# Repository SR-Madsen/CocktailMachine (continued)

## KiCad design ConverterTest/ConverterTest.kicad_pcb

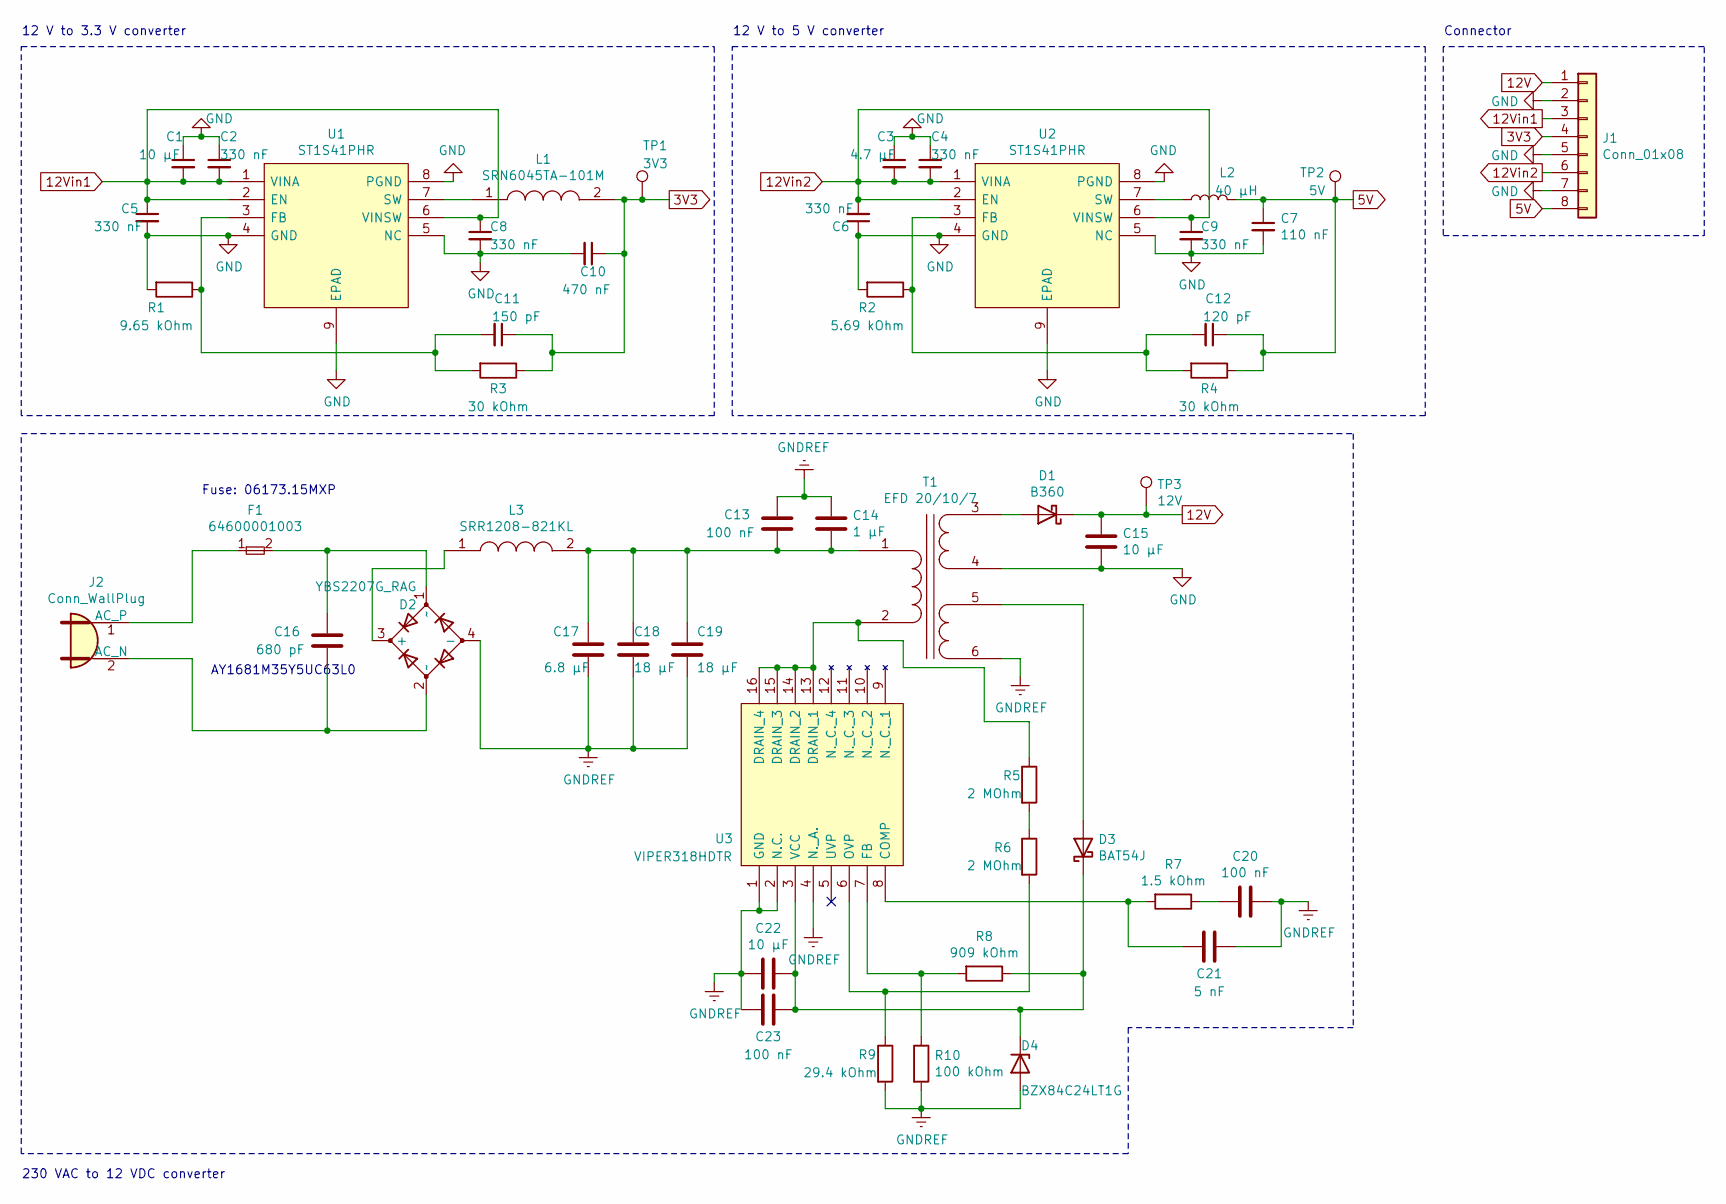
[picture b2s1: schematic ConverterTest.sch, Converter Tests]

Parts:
C1, C15, C22: 10 µF; C_1206_3216Metric
C2, C4, C5, C6, C8, C9: 330 nF; C_0603_1608Metric
C3: 4.7 µF; C_0805_2012Metric
C7: 110 nF; C_0603_1608Metric
C10: 470 nF; C_0603_1608Metric
C11: 150 pF; C_0603_1608Metric
C12: 120 pF; C_0603_1608Metric
C13: 100 nF; C_1210_3225Metric
C14: 1 µF; C_Rect_L24.0mm_W10.1mm_P22.50mm_MKT
C16: 680 pF; C_Disc_D8.0mm_W5.0mm_P10.00mm
C17: 6.8 µF; CP_Radial_D10.0mm_P5.00mm
C18, C19: 18 µF; CP_Radial_D12.5mm_P5.00mm
C20, C23: 100 nF; C_0603_1608Metric
C21: 5 nF; C_0603_1608Metric
D1: B360; D_SMC
D2: YBS2207G_RAG; Mouser Part Number 821-YBS2207GRAG
D3: BAT54J; D_SOD-323F
D4: BZX84C24LT1G; D_SOT-23_ANK
F1: 64600001003; Mouser Part Number 576-64600001003
J1: Conn_01x08; PinHeader_1x08_P2.54mm_Vertical
J2: Conn_WallPlug; PinHeader_1x02_P2.54mm_Vertical
L1: SRN6045TA-101M; Mouser Part Number 652-SRN6045TA-101M
L2: 40 µH; L_Bourns-SRN4018
L3: SRR1208-821KL; Mouser Part Number 652-SRR1208-821KL
R1: 9.65 kOhm; R_0603_1608Metric
R2: 5.69 kOhm; R_0603_1608Metric
R3, R4: 30 kOhm; R_0603_1608Metric
R5, R6: 2 MOhm; R_1206_3216Metric
R7: 1.5 kOhm; R_0603_1608Metric
R8: 909 kOhm; R_0603_1608Metric
R9: 29.4 kOhm; R_0603_1608Metric
R10: 100 kOhm; R_0603_1608Metric
T1: EFD 20/10/7; EFD_20_10_7
TP1: 3V3; TestPoint_Pad_D2.0mm
TP2: 5V; TestPoint_Pad_D2.0mm
TP3: 12V; TestPoint_Pad_D2.0mm
U1, U2: ST1S41PHR; Manufacturer_Part_Number ST1S41PHR
U3: VIPER318HDTR; Manufacturer_Part_Number VIPER318HDTR

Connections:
3V3: C10.1, C11.1, J1.4, L1.2, R3.1, TP1.1
5V: C7.1, C12.1, J1.8, L2.2, R4.1, TP2.1
12V: C15.1, D1.1 (K), J1.1, TP3.1
12Vin1: C1.2, C2.2, C5.1, C8.1, J1.3, U1.1 (VINA), U1.2 (EN), U1.6 (VINSW)
12Vin2: C3.2, C4.2, C6.2, C9.1, J1.6, U2.1 (VINA), U2.2 (EN), U2.6 (VINSW)
GND: C1.1, C2.1, C3.1, C4.1, C5.2, C6.1, C7.2, C8.2, C9.2, C10.2, C15.2, J1.2, J1.5, J1.7, R1.2, R2.2, T1.4 (SB), U1.4 (GND), U1.5 (NC), U1.8 (PGND), U1.9 (EPAD), U2.4 (GND), U2.5 (NC), U2.8 (PGND), U2.9 (EPAD)
GNDREF: C13.1, C14.1, C17.2, C18.2, C19.2, C20.1, C21.1, C22.2, C23.2, D2.4 (-), D4.2 (A), R9.2, R10.2, T1.6 (SD), U3.1 (GND), U3.2 (N.C.), U3.4 (N._A.)
unnamed: C11.2, R1.1, R3.2, U1.3 (FB)
unnamed: C12.2, R2.1, R4.2, U2.3 (FB)
unnamed: C13.2, C14.2, C17.1, C18.1, C19.1, L3.2, T1.1 (AA)
unnamed: C16.1, D2.1 (~~), F1.2
unnamed: C16.2, D2.2 (~~), J2.2 (AC_N)
unnamed: C20.2, R7.1
unnamed: C21.2, R7.2, U3.8 (COMP)
unnamed: C22.1, C23.1, D3.1 (K), D4.1 (K), R8.1, U3.3 (VCC)
unnamed: D1.2 (A), T1.3 (SA)
unnamed: D2.3 (+), L3.1
unnamed: D3.2 (A), T1.5 (SC)
unnamed: F1.1, J2.1 (AC_P)
unnamed: L1.1, U1.7 (SW)
unnamed: L2.1, U2.7 (SW)
unnamed: R5.1, T1.2 (AB), U3.13 (DRAIN_1), U3.14 (DRAIN_2), U3.15 (DRAIN_3), U3.16 (DRAIN_4)
unnamed: R5.2, R6.1
unnamed: R6.2, R9.1, U3.6 (OVP)
unnamed: R8.2, R10.1, U3.7 (FB)

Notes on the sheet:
12 V to 3.3 V converter
12 V to 5 V converter
Fuse: 06173.15MXP
AY1681M35Y5UC63L0
230 VAC to 12 VDC converter
Connector

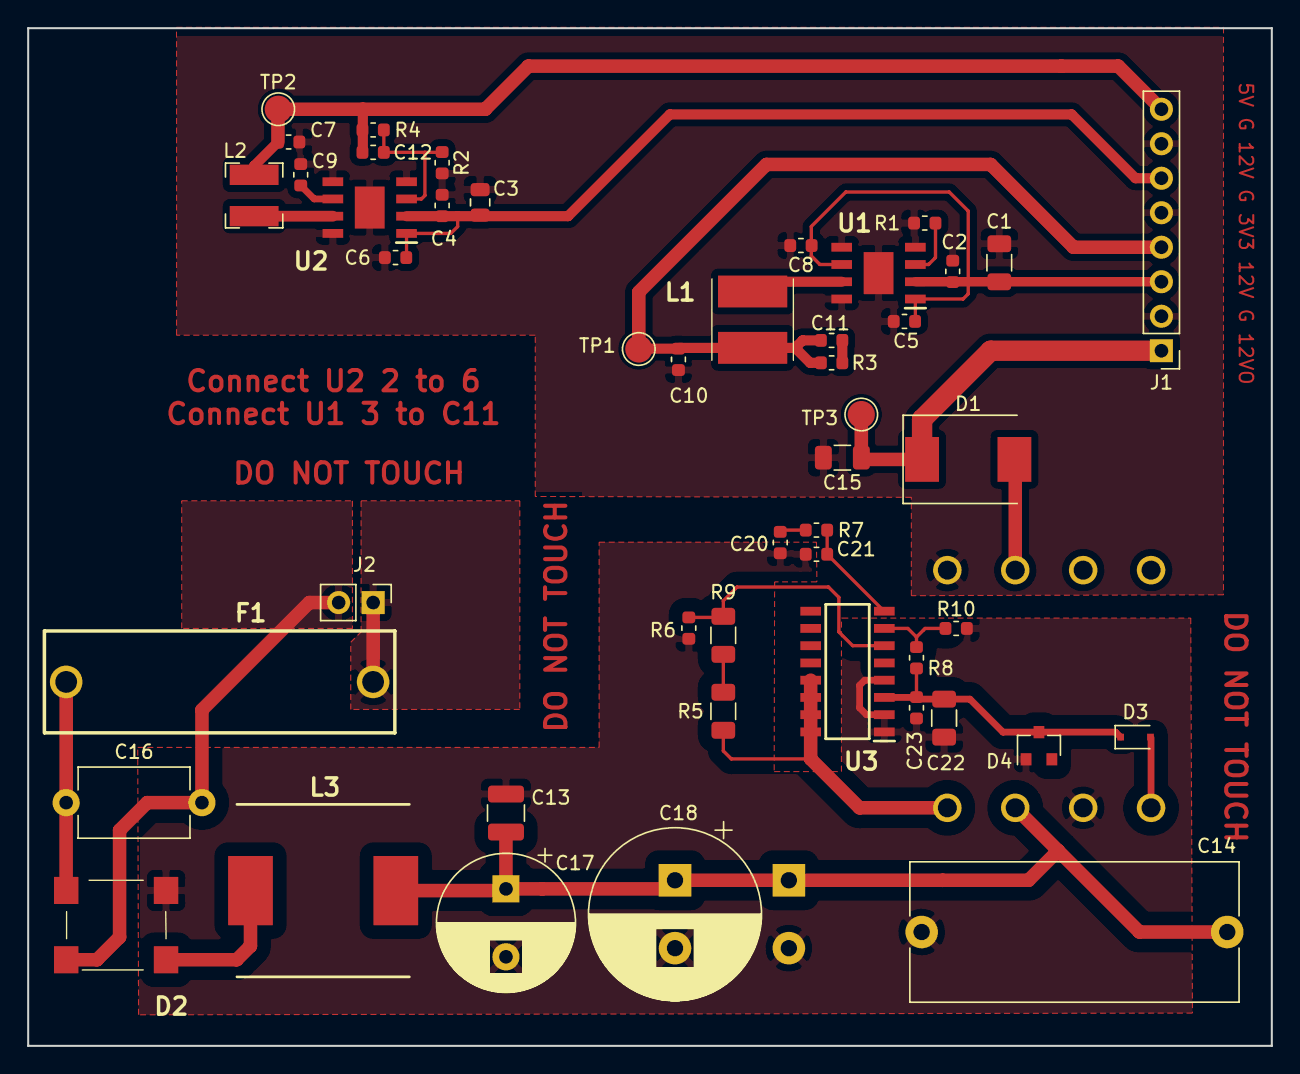
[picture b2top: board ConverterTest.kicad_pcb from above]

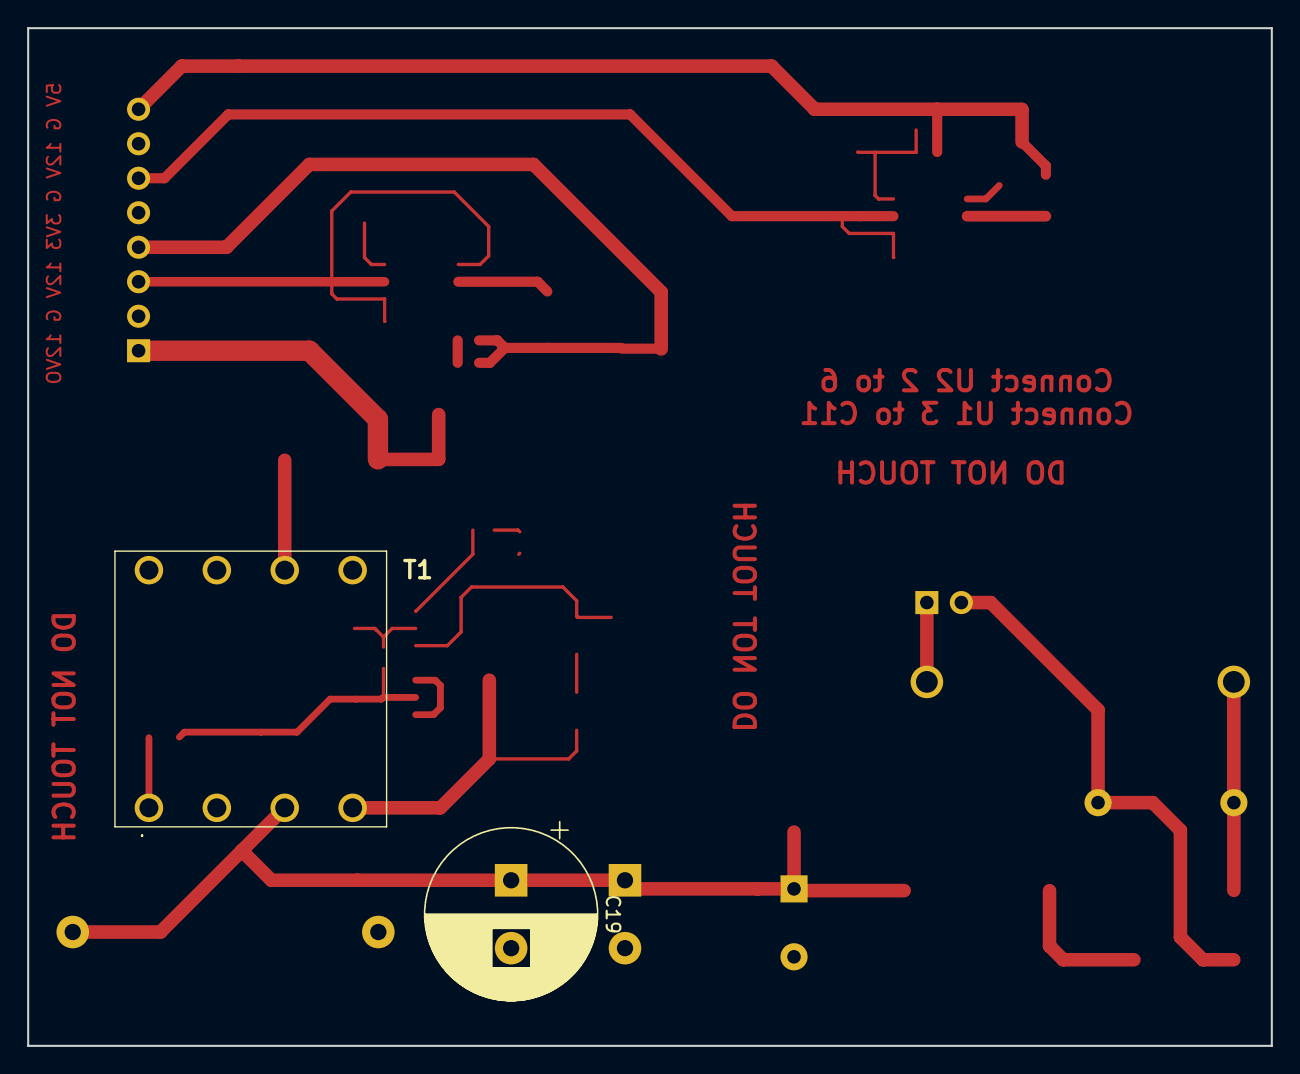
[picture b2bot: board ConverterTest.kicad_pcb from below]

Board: 2 copper layers, 91.6 x 74.9 mm, 50 parts (2 on the bottom side), 25 nets.

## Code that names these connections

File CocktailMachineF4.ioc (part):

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PB13.GPIOParameters=GPIO_PuPd,GPIO_Label
PB10.Mode=Single Bank 1
PG4.Signal=FMC_A14_BA0
PG8.Signal=FMC_SDCLK
PC12.Signal=UART5_TX
PB14.GPIO_Label=LCD_BL_CTRL
PG0.Signal=FMC_A10
PA6.GPIO_Label=LED_YELLOW
PB13.Signal=GPIO_Input
PE6.GPIO_Label=PUMP4_ON
RCC.SYSCLKSource=RCC_SYSCLKSOURCE_PLLCLK
PF7.Signal=QUADSPI_BK1_IO2
PB6.Signal=I2C1_SCL
PB12.PinState=GPIO_PIN_SET
PH1/OSC_OUT.Signal=RCC_OSC_OUT
PB6.Mode=I2C
PC3.Signal=FMC_SDCKE0
PD0.Signal=FMC_D2_DA2
PD8.Signal=FMC_D13_DA13
PE5.Signal=GPIO_Output
PE1.Signal=FMC_NBL1
PB3.Mode=JTAG_5_pins
PB12.GPIO_Label=DSI_RESET
PE9.Signal=FMC_D6_DA6
PA5.GPIO_PuPd=GPIO_PULLDOWN
PE4.GPIO_Label=PUMP2_ON
PF8.Mode=Single Bank 1
PF3.Signal=FMC_A3
PE10.Signal=FMC_D7_DA7
PC8.GPIOParameters=GPIO_Speed,GPIO_Label
Mcu.Package=LQFP176
PA5.GPIOParameters=GPIO_PuPd,GPIO_Label
PC8.GPIO_Speed=GPIO_SPEED_FREQ_LOW
PB14.GPIOParameters=GPIO_Label
PF14.Signal=FMC_A8
PF10.Mode=Single Bank 1
PE6.GPIO_PuPd=GPIO_PULLDOWN
PD15.Signal=FMC_D1_DA1
PA6.GPIOParameters=GPIO_Label
PG5.Signal=FMC_A15_BA1
PC2.Signal=FMC_SDNE0
PD1.Signal=FMC_D3_DA3
PC0.Signal=FMC_SDNWE
PD10.Signal=FMC_D15_DA15
PB11.Mode=DSIHost_Adapted_TE
PB10.Signal=QUADSPI_BK1_NCS
PB14.Signal=GPIO_Input
PA5.Signal=GPIO_Output
PC12.Mode=Asynchronous
PB13.GPIO_PuPd=GPIO_NOPULL
PE14.Signal=FMC_D11_DA11
PE15.Signal=FMC_D12_DA12
PE8.Signal=FMC_D5_DA5
PF13.Signal=FMC_A7
PA13.Mode=JTAG_5_pins
PE4.GPIO_PuPd=GPIO_PULLDOWN
PA5.GPIO_Label=LED_RED
PE5.GPIO_Label=PUMP3_ON
PF6.Mode=Single Bank 1
PF9.Signal=QUADSPI_BK1_IO1
PE3.Signal=GPIO_Output
PF4.Signal=FMC_A4
PD2.Signal=UART5_RX
PB12.GPIO_PuPd=GPIO_PULLUP
PA7.GPIOParameters=GPIO_Label
PB12.GPIOParameters=GPIO_Speed,PinState,GPIO_PuPd,GPIO_Label
PC3.Mode=SdramChipSelect1_1
Mcu.UserName=STM32F469IITx
PB13.GPIO_Label=LCD_INT
PB11.Signal=DSIHOST_TE
PG15.Signal=FMC_SDNCAS
PE5.GPIOParameters=GPIO_PuPd,GPIO_Label
PE4.GPIOParameters=GPIO_PuPd,GPIO_Label
PE5.GPIO_PuPd=GPIO_PULLDOWN
PH0/OSC_IN.Mode=HSE-External-Oscillator
PF12.Signal=FMC_A6
RCC.HSE_VALUE=10000000
PA15.Mode=JTAG_5_pins
PF9.Mode=Single Bank 1
PB4.Mode=JTAG_5_pins
PE13.Signal=FMC_D10_DA10
PA14.Mode=JTAG_5_pins
PF11.Signal=FMC_SDNRAS
PE3.GPIOParameters=GPIO_Label
PB7.Signal=I2C1_SDA
PE4.Signal=GPIO_Output
PH1/OSC_OUT.Mode=HSE-External-Oscillator
PE6.GPIOParameters=GPIO_PuPd,GPIO_Label
PA6.Signal=GPIO_Output
PA15.Signal=SYS_JTDI
PF8.Signal=QUADSPI_BK1_IO0
PF5.Signal=FMC_A5
PF0.Signal=FMC_A0
PE7.Signal=FMC_D4_DA4
PB4.Signal=SYS_JTRST
PA3.Signal=ADCx_IN3
PG1.Signal=FMC_A11
PC8.Signal=GPIO_Output
PC2.Mode=SdramChipSelect1_1
PD9.Signal=FMC_D14_DA14
PC8.GPIO_Label=BT_RESET
PA13.Signal=SYS_JTMS-SWDIO
PF7.Mode=Single Bank 1
PF6.Signal=QUADSPI_BK1_IO3
PF2.Signal=FMC_A2
PE11.Signal=FMC_D8_DA8
PB12.GPIO_Speed=GPIO_SPEED_FREQ_VERY_HIGH
PD2.Mode=Asynchronous
board=custom
PH0/OSC_IN.Signal=RCC_OSC_IN
PF10.Signal=QUADSPI_CLK
PF15.Signal=FMC_A9
PF1.Signal=FMC_A1
PE6.Signal=GPIO_Output
Mcu.Name=STM32F469IITx
PE0.Signal=FMC_NBL0
PE12.Signal=FMC_D9_DA9
PD14.Signal=FMC_D0_DA0
PB3.Signal=SYS_JTDO-SWO
RCC.SYSCLKFreq_VALUE=180000000
PA7.GPIO_Label=LED_GREEN
PB7.Mode=I2C
PA14.Signal=SYS_JTCK-SWCLK
PE3.GPIO_Label=PUMP1_ON
PB12.Signal=GPIO_Output
PA7.Signal=GPIO_Output

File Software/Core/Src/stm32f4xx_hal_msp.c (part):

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
    __HAL_RCC_GPIOA_CLK_ENABLE();
    /**ADC1 GPIO Configuration
    PA3     ------> ADC1_IN3
    */
    GPIO_InitStruct.Pin = GPIO_PIN_3;
    GPIO_InitStruct.Mode = GPIO_MODE_ANALOG;
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    __HAL_RCC_ADC1_CLK_DISABLE();

    /**ADC1 GPIO Configuration
    PA3     ------> ADC1_IN3
    */
    HAL_GPIO_DeInit(GPIOA, GPIO_PIN_3);

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
    __HAL_RCC_GPIOB_CLK_ENABLE();
    /**DSIHOST GPIO Configuration
    PB11     ------> DSIHOST_TE
    */
    GPIO_InitStruct.Pin = GPIO_PIN_11;
    GPIO_InitStruct.Mode = GPIO_MODE_AF_PP;
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    __HAL_RCC_DSI_CLK_DISABLE();

    /**DSIHOST GPIO Configuration
    PB11     ------> DSIHOST_TE
    */
    HAL_GPIO_DeInit(GPIOB, GPIO_PIN_11);

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
    __HAL_RCC_GPIOB_CLK_ENABLE();
    /**I2C1 GPIO Configuration
    PB6     ------> I2C1_SCL
    PB7     ------> I2C1_SDA
    */
    GPIO_InitStruct.Pin = GPIO_PIN_6|GPIO_PIN_7;
    GPIO_InitStruct.Mode = GPIO_MODE_AF_OD;
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    __HAL_RCC_I2C1_CLK_DISABLE();

    /**I2C1 GPIO Configuration
    PB6     ------> I2C1_SCL
    PB7     ------> I2C1_SDA
    */
    HAL_GPIO_DeInit(GPIOB, GPIO_PIN_6);

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    __HAL_RCC_GPIOF_CLK_ENABLE();
    __HAL_RCC_GPIOB_CLK_ENABLE();
    /**QUADSPI GPIO Configuration
    PF6     ------> QUADSPI_BK1_IO3
    PF7     ------> QUADSPI_BK1_IO2
    PF8     ------> QUADSPI_BK1_IO0
    PF9     ------> QUADSPI_BK1_IO1
    PF10     ------> QUADSPI_CLK
    PB10     ------> QUADSPI_BK1_NCS
    */
    GPIO_InitStruct.Pin = GPIO_PIN_6|GPIO_PIN_7|GPIO_PIN_10;
    GPIO_InitStruct.Mode = GPIO_MODE_AF_PP;
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    __HAL_RCC_QSPI_CLK_DISABLE();

    /**QUADSPI GPIO Configuration
    PF6     ------> QUADSPI_BK1_IO3
    PF7     ------> QUADSPI_BK1_IO2
    PF8     ------> QUADSPI_BK1_IO0
    PF9     ------> QUADSPI_BK1_IO1
    PF10     ------> QUADSPI_CLK
    PB10     ------> QUADSPI_BK1_NCS
    */
    HAL_GPIO_DeInit(GPIOF, GPIO_PIN_6|GPIO_PIN_7|GPIO_PIN_8|GPIO_PIN_9
                          |GPIO_PIN_10);
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    __HAL_RCC_GPIOC_CLK_ENABLE();
    __HAL_RCC_GPIOD_CLK_ENABLE();
    /**UART5 GPIO Configuration
    PC12     ------> UART5_TX
    PD2     ------> UART5_RX
    */
    GPIO_InitStruct.Pin = GPIO_PIN_12;
    GPIO_InitStruct.Mode = GPIO_MODE_AF_PP;
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    __HAL_RCC_UART5_CLK_DISABLE();

    /**UART5 GPIO Configuration
    PC12     ------> UART5_TX
    PD2     ------> UART5_RX
    */
    HAL_GPIO_DeInit(GPIOC, GPIO_PIN_12);

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  __HAL_RCC_FMC_CLK_ENABLE();

  /** FMC GPIO Configuration
  PF0   ------> FMC_A0
  PF1   ------> FMC_A1
  PF2   ------> FMC_A2
  PF3   ------> FMC_A3
  PF4   ------> FMC_A4
  PF5   ------> FMC_A5
  PC0   ------> FMC_SDNWE
  PC2   ------> FMC_SDNE0
  PC3   ------> FMC_SDCKE0
  PF11   ------> FMC_SDNRAS
  PF12   ------> FMC_A6
  PF13   ------> FMC_A7
  PF14   ------> FMC_A8
  PF15   ------> FMC_A9
  PG0   ------> FMC_A10
  PG1   ------> FMC_A11
  PE7   ------> FMC_D4
  PE8   ------> FMC_D5
  PE9   ------> FMC_D6
  PE10   ------> FMC_D7
  PE11   ------> FMC_D8
  PE12   ------> FMC_D9
  PE13   ------> FMC_D10
  PE14   ------> FMC_D11
  PE15   ------> FMC_D12
  PD8   ------> FMC_D13
  PD9   ------> FMC_D14
  PD10   ------> FMC_D15
  PD14   ------> FMC_D0
  PD15   ------> FMC_D1
  PG4   ------> FMC_BA0
  PG5   ------> FMC_BA1
  PG8   ------> FMC_SDCLK
  PD0   ------> FMC_D2
  PD1   ------> FMC_D3
  PG15   ------> FMC_SDNCAS
  PE0   ------> FMC_NBL0
  PE1   ------> FMC_NBL1
  */
  GPIO_InitStruct.Pin = GPIO_PIN_0|GPIO_PIN_1|GPIO_PIN_2|GPIO_PIN_3
                          |GPIO_PIN_4|GPIO_PIN_5|GPIO_PIN_11|GPIO_PIN_12
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  __HAL_RCC_FMC_CLK_DISABLE();

  /** FMC GPIO Configuration
  PF0   ------> FMC_A0
  PF1   ------> FMC_A1
  PF2   ------> FMC_A2
  PF3   ------> FMC_A3
  PF4   ------> FMC_A4
  PF5   ------> FMC_A5
  PC0   ------> FMC_SDNWE
  PC2   ------> FMC_SDNE0
  PC3   ------> FMC_SDCKE0
  PF11   ------> FMC_SDNRAS
  PF12   ------> FMC_A6
  PF13   ------> FMC_A7
  PF14   ------> FMC_A8
  PF15   ------> FMC_A9
  PG0   ------> FMC_A10
  PG1   ------> FMC_A11
  PE7   ------> FMC_D4
  PE8   ------> FMC_D5
  PE9   ------> FMC_D6
  PE10   ------> FMC_D7
  PE11   ------> FMC_D8
  PE12   ------> FMC_D9
  PE13   ------> FMC_D10
  PE14   ------> FMC_D11
  PE15   ------> FMC_D12
  PD8   ------> FMC_D13
  PD9   ------> FMC_D14
  PD10   ------> FMC_D15
  PD14   ------> FMC_D0
  PD15   ------> FMC_D1
  PG4   ------> FMC_BA0
  PG5   ------> FMC_BA1
  PG8   ------> FMC_SDCLK
  PD0   ------> FMC_D2
  PD1   ------> FMC_D3
  PG15   ------> FMC_SDNCAS
  PE0   ------> FMC_NBL0
  PE1   ------> FMC_NBL1
  */
  HAL_GPIO_DeInit(GPIOF, GPIO_PIN_0|GPIO_PIN_1|GPIO_PIN_2|GPIO_PIN_3
                          |GPIO_PIN_4|GPIO_PIN_5|GPIO_PIN_11|GPIO_PIN_12
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
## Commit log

2020-09-16 Added STM32CubeMX configuration file.
2020-10-24 Added finished PCB for project. Requires review.
2020-10-25 Changed ferrite beads to ones with adequate max currents. Changed JTAG connector to 20-pin standard. Minor PCB fixes.
2020-10-26 Made changes to PCB (added many planes/polygons instead of traces, increased amount of vias, increased trace sizes).
2020-10-31 Added new JTAG/UART header with connections for STLink V3. Moved from SamacSys to personal GitHub-based library.
2020-10-31 Fixed error made during STM32CubeMX configuration.
2020-10-31 Updated schematic descriptions. Added converter test PCB.
2020-10-31 Fixed FMC related error in MX file and added ADC pin. Added connector and filter for external sensor.
2020-10-31 Forgot to save before commit.
2020-11-01 Final fixes to PCB silk screen and via layout.
2020-11-01 Alterations to voltage regulator circuits for improved performance.
2020-11-02 Added isolation air gap to transformer.
2020-11-23 Very minor changes to layout to make it prettier.
2020-11-24 Added silk screen text.
2020-11-27 Prettified the PCB, minor changes to routing.
2020-11-28 Info cache.
2020-11-30 Minor changes to CubeMX. Generated code for IDE, added TouchGFX GUI and code. Begun work on board bring-up code.
2020-12-06 Further work on implementing all drivers. LCD drivers have been implemented. Flash loader is up next, as well as AL.
2021-01-09 Removed guard ring from crystal.
2021-01-11 Added datasheets, reference manuals, and application notes for used ICs.
2021-08-16 Updated and added working demo. Restarted TouchGFX project.
2021-08-30 Rebuilt project for better folder structure. Started work on peripheral drivers (BSP) and HAL.
2022-05-02 Added documentation.
